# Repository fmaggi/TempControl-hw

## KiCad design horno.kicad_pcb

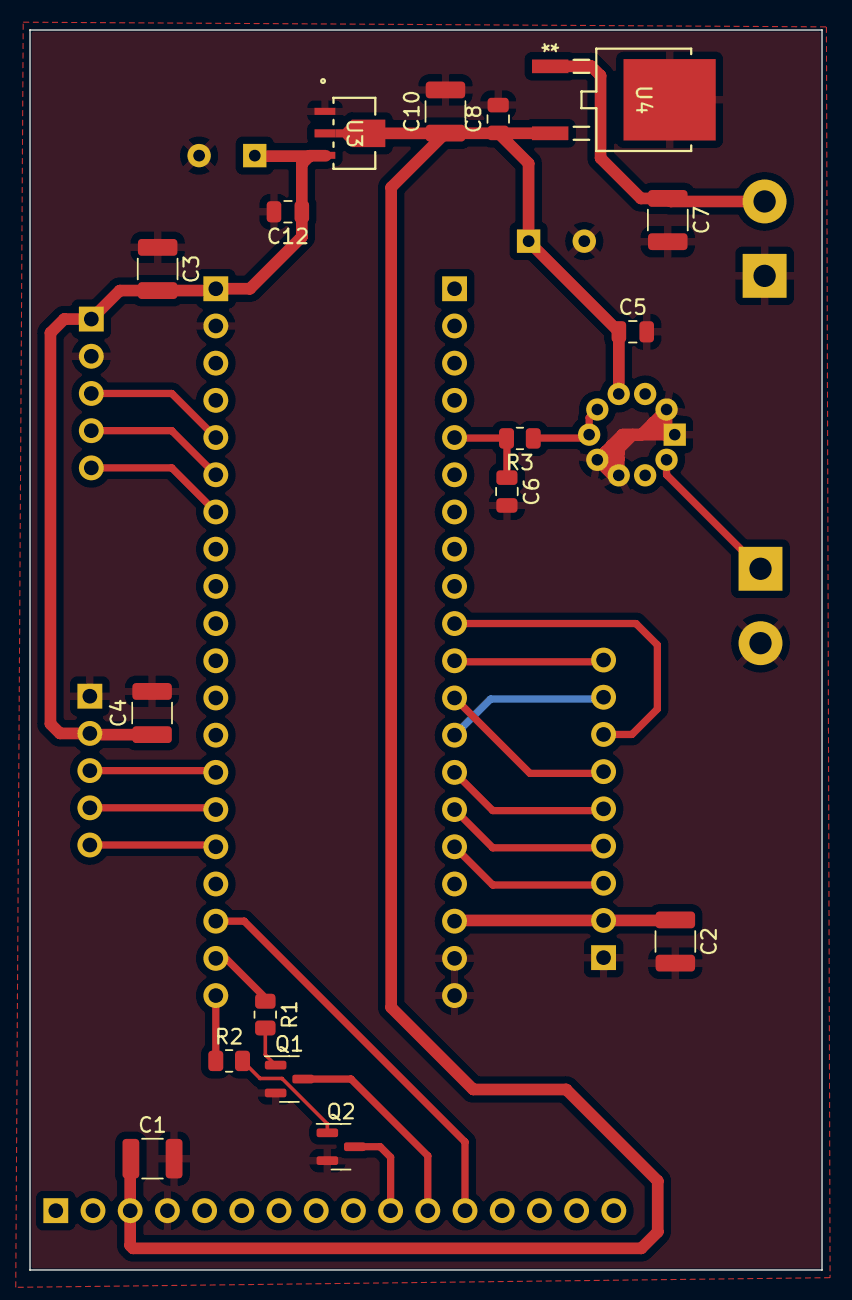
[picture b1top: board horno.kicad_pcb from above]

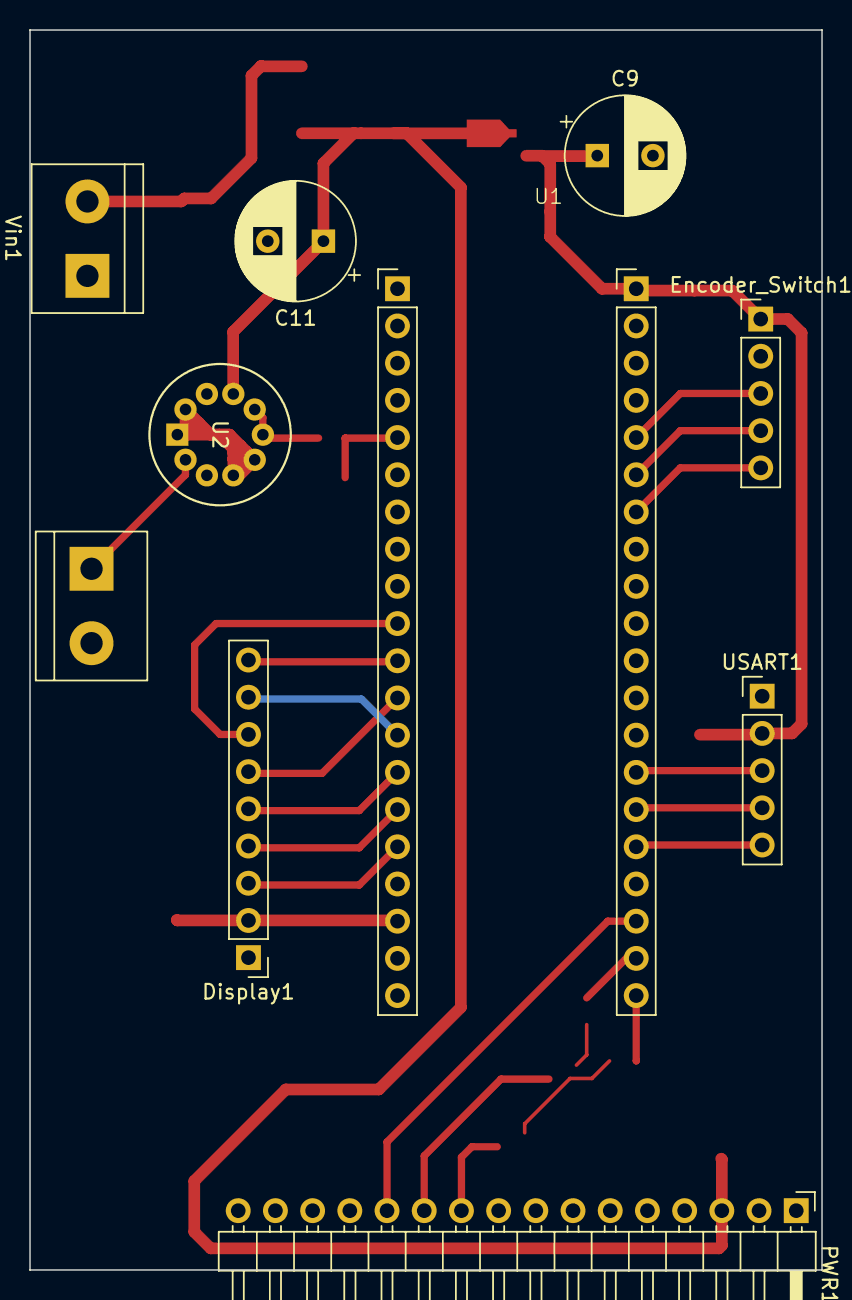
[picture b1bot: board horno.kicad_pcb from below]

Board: 2 copper layers, 54.1 x 84.7 mm, 27 parts (10 on the bottom side), 27 nets.

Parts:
C1, C2, C3, C4, C7, C10: 100n; C_1210_3225Metric
C5: 0.01u; C_0805_2012Metric
C6: 470n; C_0805_2012Metric
C8, C12: 0.1u; C_0805_2012Metric
C9, C11: 47u; CP_Radial_D8.0mm_P3.80mm
Display1: Conn_01x09_Pin; PinHeader_1x09_P2.54mm_Vertical
Encoder_Switch1: Conn_01x05_Pin; PinHeader_1x05_P2.54mm_Vertical
PWR1: Conn_01x16_Pin; PinHeader_1x16_P2.54mm_Horizontal
Q1, Q2: BC848; SOT-23
R1, R2: 4.7k; R_0805_2012Metric
R3: 33k; R_0805_2012Metric
TC1: Thermocouple; TerminalBlock_bornier-2_P5.08mm
U1: STM32F103C8Tx; blue_pill
U2: AD596AHZ; ad596
U3: MCP1700T-3302E/MB; SOT-89_3MC_MCH
U4: L78M05CDT-TR; DPAK_STM
USART1: Conn_01x05_Pin; PinHeader_1x05_P2.54mm_Vertical
Vin1: Conn_01x02; TerminalBlock_bornier-2_P5.08mm

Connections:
0: C1.2, C2.2, C3.1, C4.2, C5.2, C6.2, C7.2, C8.2, C9.2, C10.2, C11.2, C12.2, Display1.1, Encoder_Switch1.2, PWR1.4, Q1.2 (E), Q2.2 (E), TC1.2 (-), U1.23 (VSS), U2.1 (-IN), U2.4 (GND), U2.5 (V-), U2.10 (-ALM), U3.1 (GND), U4.3 (GROUND), USART1.1, Vin1.1
3.3V: C2.1, C3.2, C4.1, C9.1, C12.1, Display1.2, Encoder_Switch1.1, U1.24 (VDD), U3.3 (VOUT), USART1.2
5V: C1.1, C5.1, C8.1, C10.1, C11.1, PWR1.3, U2.8 (V+), U3.2 (VIN), U4.2 (OUTPUT)
IN_CH1: Encoder_Switch1.5, U1.42 (PB6)
IN_CH2: Encoder_Switch1.4, U1.43 (PB7)
IN_OK: Encoder_Switch1.3, U1.45 (PB8)
LCD_CLK: Display1.7, U1.15 (PA5)
LCD_CS: Display1.3, U1.22 (PB11)
LCD_DC: Display1.5, U1.19 (PB1)
LCD_LED: Display1.8, U1.18 (PB0)
LCD_MISO: Display1.9, U1.16 (PA6)
LCD_MOSI: Display1.6, U1.17 (PA7)
LCD_RST: Display1.4, U1.21 (PB10)
unnamed: Q1.1 (B), R1.2
unnamed: Q2.1 (B), R2.2
unnamed: TC1.1 (+), U2.2 (+IN)
unnamed: R2.1, U1.25 (PB12)
unnamed: R1.1, U1.26 (PB13)
unnamed: R3.1, U2.6 (FB), U2.7 (VOUT)
unnamed: C7.1, U4.1 (INPUT), Vin1.2
PWR_CH1: PWR1.10, Q2.3 (C)
PWR_CH2: PWR1.11, Q1.3 (C)
PWR_ZC: PWR1.12, U1.27 (PB14)
T: C6.1, R3.2, U1.10 (PA0)
USART_CLK: U1.29 (PA8), USART1.5
USART_RX: U1.31 (PA10), USART1.3
USART_TX: U1.30 (PA9), USART1.4

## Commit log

2024-02-14 gitingore
